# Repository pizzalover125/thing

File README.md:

# thing
A spotify car thing clone. If you aren't aware, Spotify recent discontinued their Car Thing. On YouTube, I spotted this video of @Ducc displaying his Car Thing Clone. I absolutely loved it, so I wanted to make my own! I added a bigger screen and a fast microcontroller to be able to display album art in the future. However, I also used cheap switches to lower the costs.

## images

## BOM
* 1x Adafruit 2" Display + 1x Adafruit 20x 6mmx6mmx6mm Push Buttons - $29.54
* 1x PCBWay PCB - $14.39
* 1x Seeed Studio XIAO ESP32C3 - $7.20

**TOTAL: $51.53**

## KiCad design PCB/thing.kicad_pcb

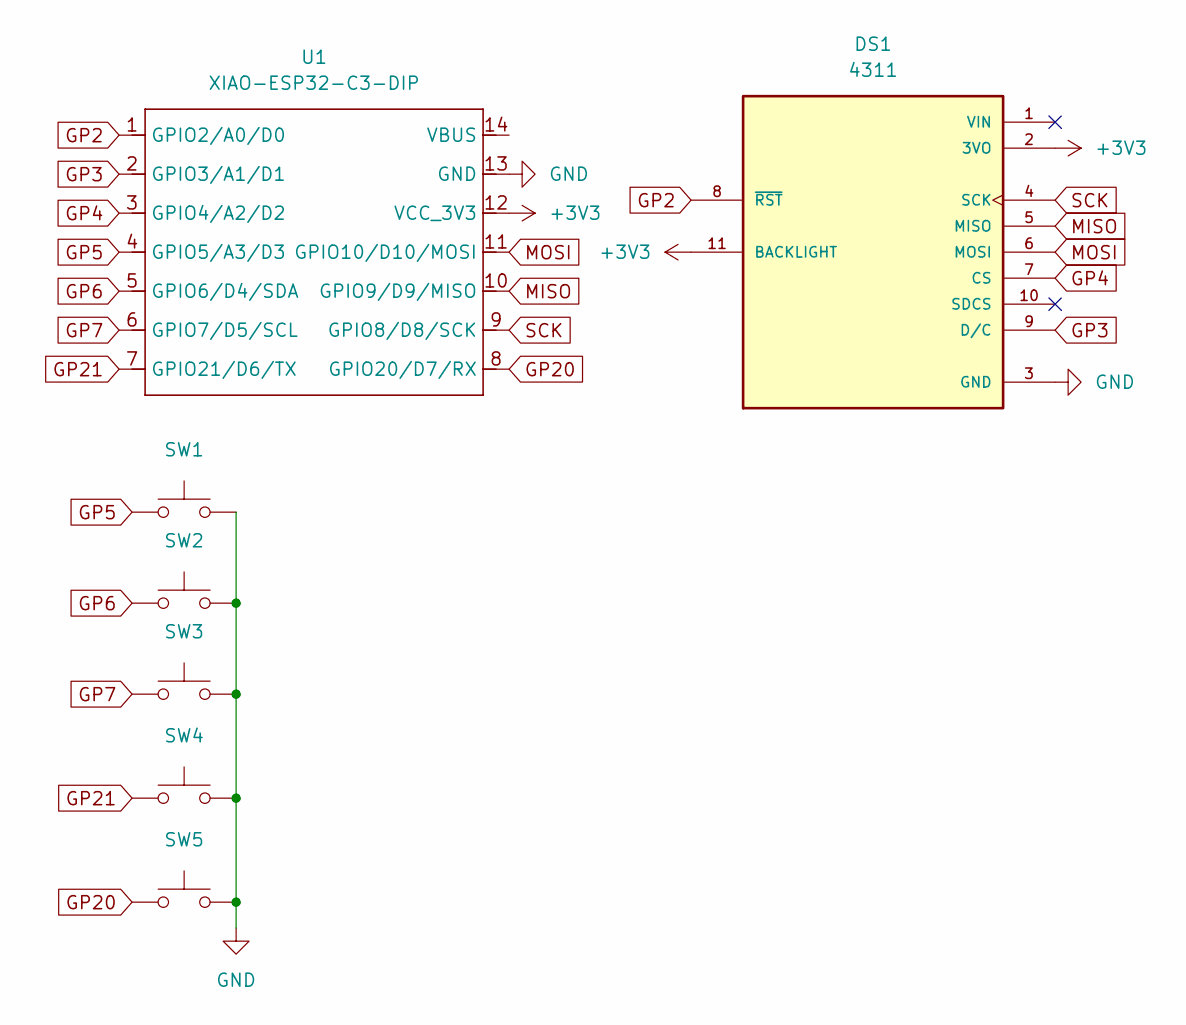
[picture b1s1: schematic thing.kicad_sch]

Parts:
DS1: 4311; MODULE_4311; PARTREV 2023-07-05
SW1, SW2, SW3, SW4, SW5: SW_Push; SW_PUSH_6mm_H4.3mm
U1: XIAO-ESP32-C3-DIP; XIAO-ESP32C3-DIP

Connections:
+3V3: DS1.2 (3VO), DS1.11 (BACKLIGHT), U1.12 (VCC_3V3)
GND: DS1.3 (GND), SW1.2, SW2.2, SW3.2, SW4.2, SW5.2, U1.13 (GND)
GP2: DS1.8 (~RST), U1.1 (GPIO2/A0/D0)
GP3: DS1.9 (D/C), U1.2 (GPIO3/A1/D1)
GP4: DS1.7 (CS), U1.3 (GPIO4/A2/D2)
GP5: SW1.1, U1.4 (GPIO5/A3/D3)
GP6: SW2.1, U1.5 (GPIO6/D4/SDA)
GP7: SW3.1, U1.6 (GPIO7/D5/SCL)
GP20: SW5.1, U1.8 (GPIO20/D7/RX)
GP21: SW4.1, U1.7 (GPIO21/D6/TX)
MISO: DS1.5 (MISO), U1.10 (GPIO9/D9/MISO)
MOSI: DS1.6 (MOSI), U1.11 (GPIO10/D10/MOSI)
SCK: DS1.4 (SCK), U1.9 (GPIO8/D8/SCK)

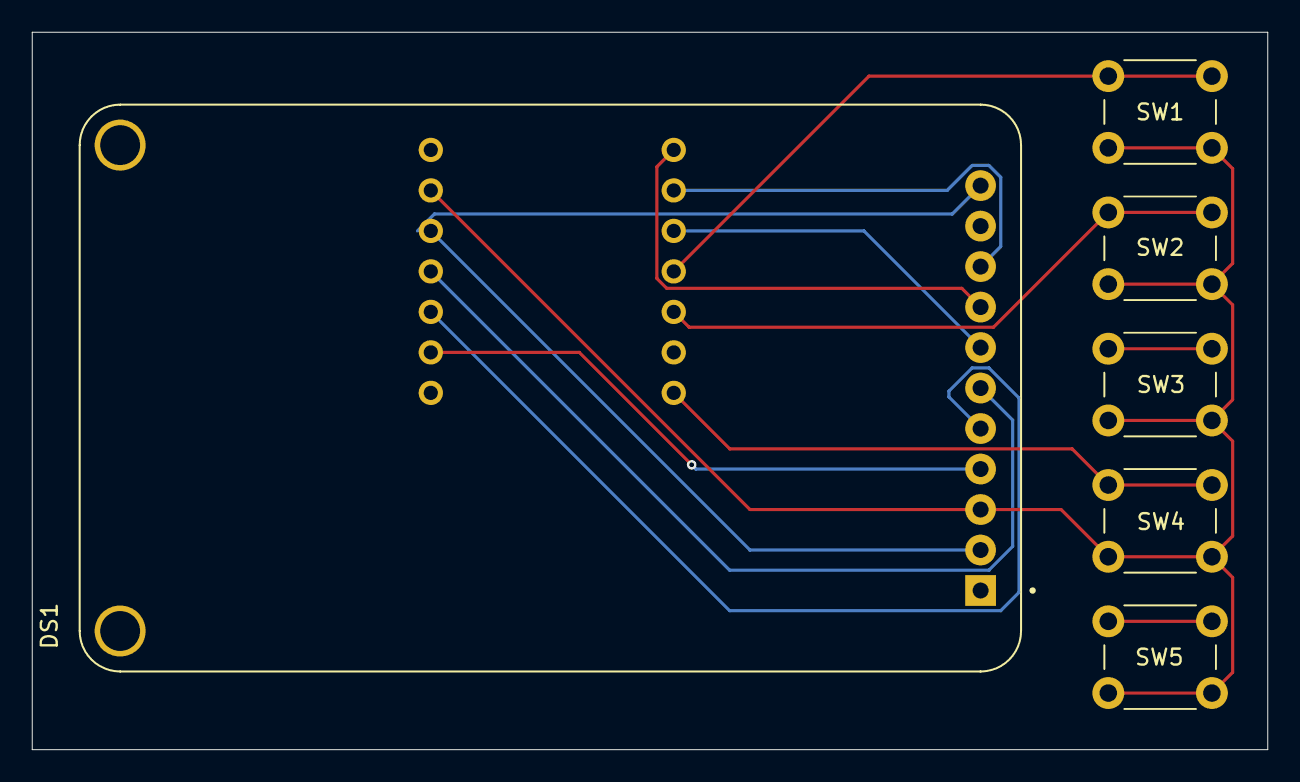
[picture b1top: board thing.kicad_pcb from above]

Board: 2 copper layers, 77.5 x 45.0 mm, 7 parts (1 on the bottom side), 13 nets.

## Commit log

2025-05-29 uploaded files
2025-07-19 added album art firmware
